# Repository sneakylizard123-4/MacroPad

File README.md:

a custom macropad designed around raspberry pi pico
made with KiCad!

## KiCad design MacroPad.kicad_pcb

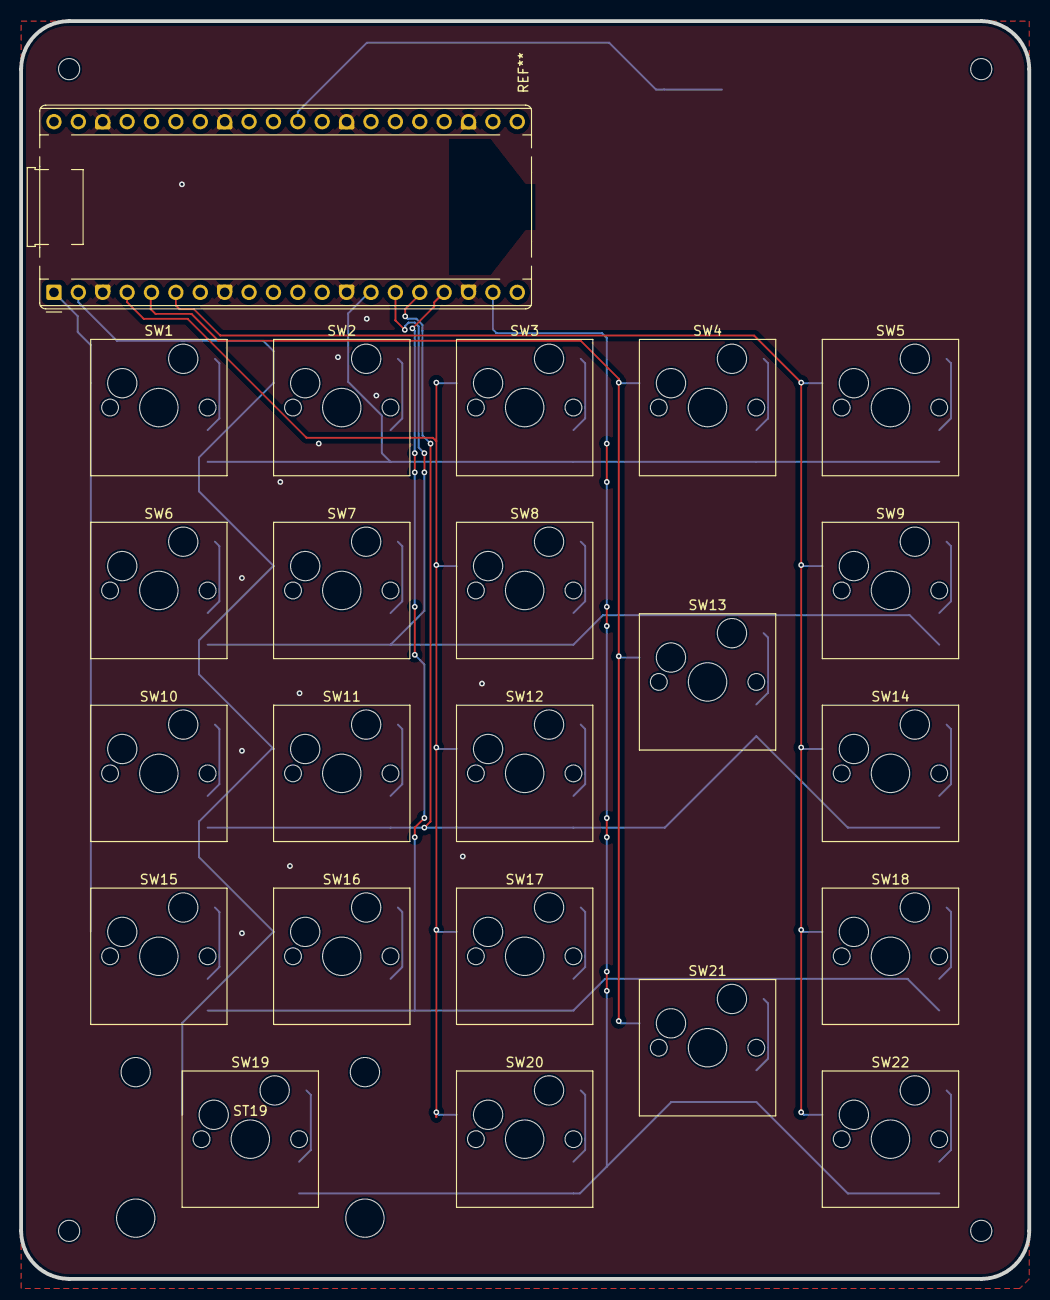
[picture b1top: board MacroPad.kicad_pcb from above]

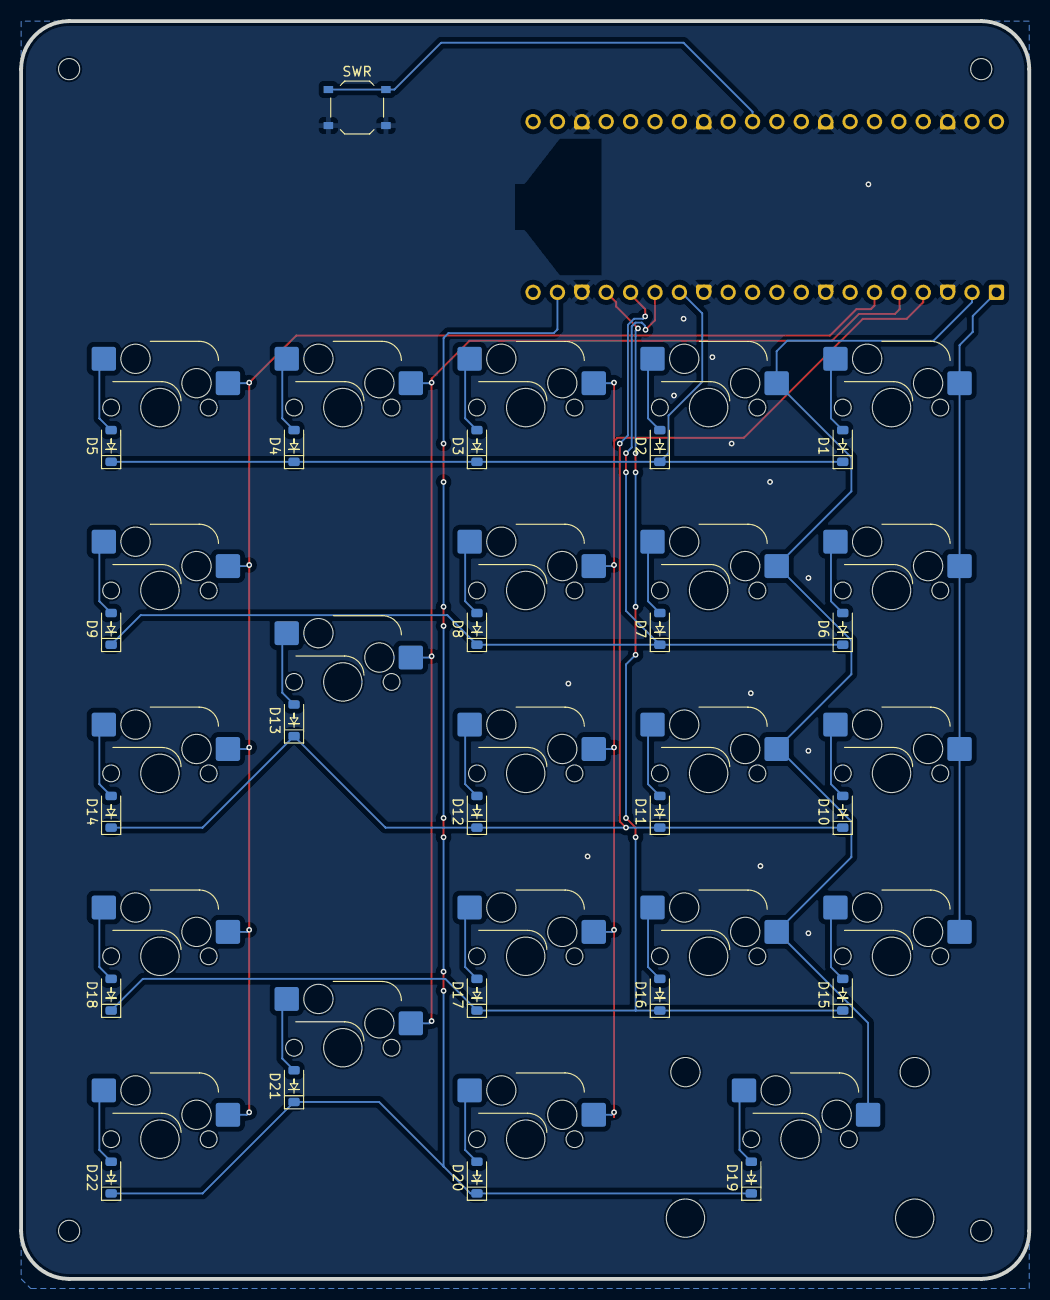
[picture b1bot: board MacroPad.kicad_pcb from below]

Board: 2 copper layers, 105.0 x 131.0 mm, 46 parts (23 on the bottom side), 32 nets.

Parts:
D1, D2, D3, D4, D5, D6, D7, D8, D9, D10, D11, D12, D13, D14, D15, D16, D17, D18, D19, D20, D21, D22: D; D_SOD-123-Stripe
ST19: MountingHole; Stabilizer_Cherry_MX_2.00u
SW1, SW2, SW3, SW4, SW5, SW6, SW7, SW8, SW9, SW10, SW11, SW12, SW13, SW14, SW15, SW16, SW17, SW18, SW20, SW21, SW22: SW_Push; SW_Hotswap_Kailh_MX_1.00u
SW19: SW_Push; SW_Hotswap_Kailh_MX_2.00u
SWR: SW_Push_1P1T_XKB_TS-1187A

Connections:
COL0: SW1.1, SW6.1, SW10.1, SW15.1
COL1: SW2.1, SW7.1, SW11.1, SW16.1, SW19.1
COL2: SW3.1, SW8.1, SW12.1, SW17.1, SW20.1
COL3: SW4.1, SW13.1, SW21.1
COL4: SW5.1, SW9.1, SW14.1, SW18.1, SW22.1
unnamed: D1.2, SW1.2
unnamed: D2.2, SW2.2
unnamed: D3.2, SW3.2
unnamed: D4.2, SW4.2
unnamed: D5.2, SW5.2
unnamed: D6.2, SW6.2
unnamed: D7.2, SW7.2
unnamed: D8.2, SW8.2
unnamed: D9.2, SW9.2
unnamed: D10.2, SW10.2
unnamed: D11.2, SW11.2
unnamed: D12.2, SW12.2
unnamed: D13.2, SW13.2
unnamed: D14.2, SW14.2
unnamed: D15.2, SW15.2
unnamed: D16.2, SW16.2
unnamed: D17.2, SW17.2
unnamed: D18.2, SW18.2
unnamed: D19.2, SW19.2
unnamed: D20.2, SW20.2
unnamed: D21.2, SW21.2
unnamed: D22.2, SW22.2
ROW0: D1.1, D2.1, D3.1, D4.1, D5.1
ROW1: D6.1, D7.1, D8.1, D9.1
ROW2: D10.1, D11.1, D12.1, D13.1, D14.1
ROW3: D15.1, D16.1, D17.1, D18.1
ROW4: D19.1, D20.1, D21.1, D22.1

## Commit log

2025-11-02 test
2025-11-02 gitignore
2025-11-02 add readme
2025-11-02 wheee
2025-11-02 bom.csv
2025-11-02 output
2025-11-02 gerbers
2025-11-02 random
2025-11-03 boom
2025-11-15 switch mcu to pico
2025-11-15 update mcu pico in vscode
2025-11-15 made with kicad
2025-11-16 update pcb
